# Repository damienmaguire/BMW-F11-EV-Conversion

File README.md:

# BMW-F11-EV-Conversion

Documenting the electronics and software side of converting a 2011 BMW 520d F11 (VIN: WBAMX12080V788571) to fully electric drive using a GS450h gearbox/inverter and ZombieVerter VCU.

## Project Goal – DDE FlexRay Emulator

The DDE (Diesel Engine Electronics) on this F11 talks to the rest of the car primarily over FlexRay. Once the diesel engine is removed, the cluster, gateway and other modules still expect to see a living DDE on the FlexRay network.

The plan is to build a small emulator that:

- Speaks FlexRay and CAN to the car
- Speaks CAN to the ZombieVerter VCU
- Translates the essential signals (RPM, coolant temp, fuel rate / power, status bits, etc.) so the car continues to behave normally
- Provides USB for programming and logging

Hardware target: one FlexRay channel + two CAN channels + USB.  
Bench development is being done with OpenFSD FlexRayRPIPanda boards and software based on dynm/pico-flexray, with SavvyCAN (flexray-phase1-capture branch) for capture and analysis.

## The DDE

- **BMW part number**: 8 513 250-01  
- **Bosch number**: 0 281 017 648  
- **Engine**: N47T 2.0 L diesel (520d)

FlexRay captures (ignition-on and engine start/stop) and later MITM logs are being used to reverse-engineer the frames the DDE sends and receives.

## FlexRay Capture Hardware / Software

- Hardware base: https://github.com/dynm/pico-flexray  
- SavvyCAN FlexRay branch: https://github.com/Tom-evnut/SavvyCAN/tree/flexray-phase1-capture  

Logs live in the `Logs/FlexRay` folder.

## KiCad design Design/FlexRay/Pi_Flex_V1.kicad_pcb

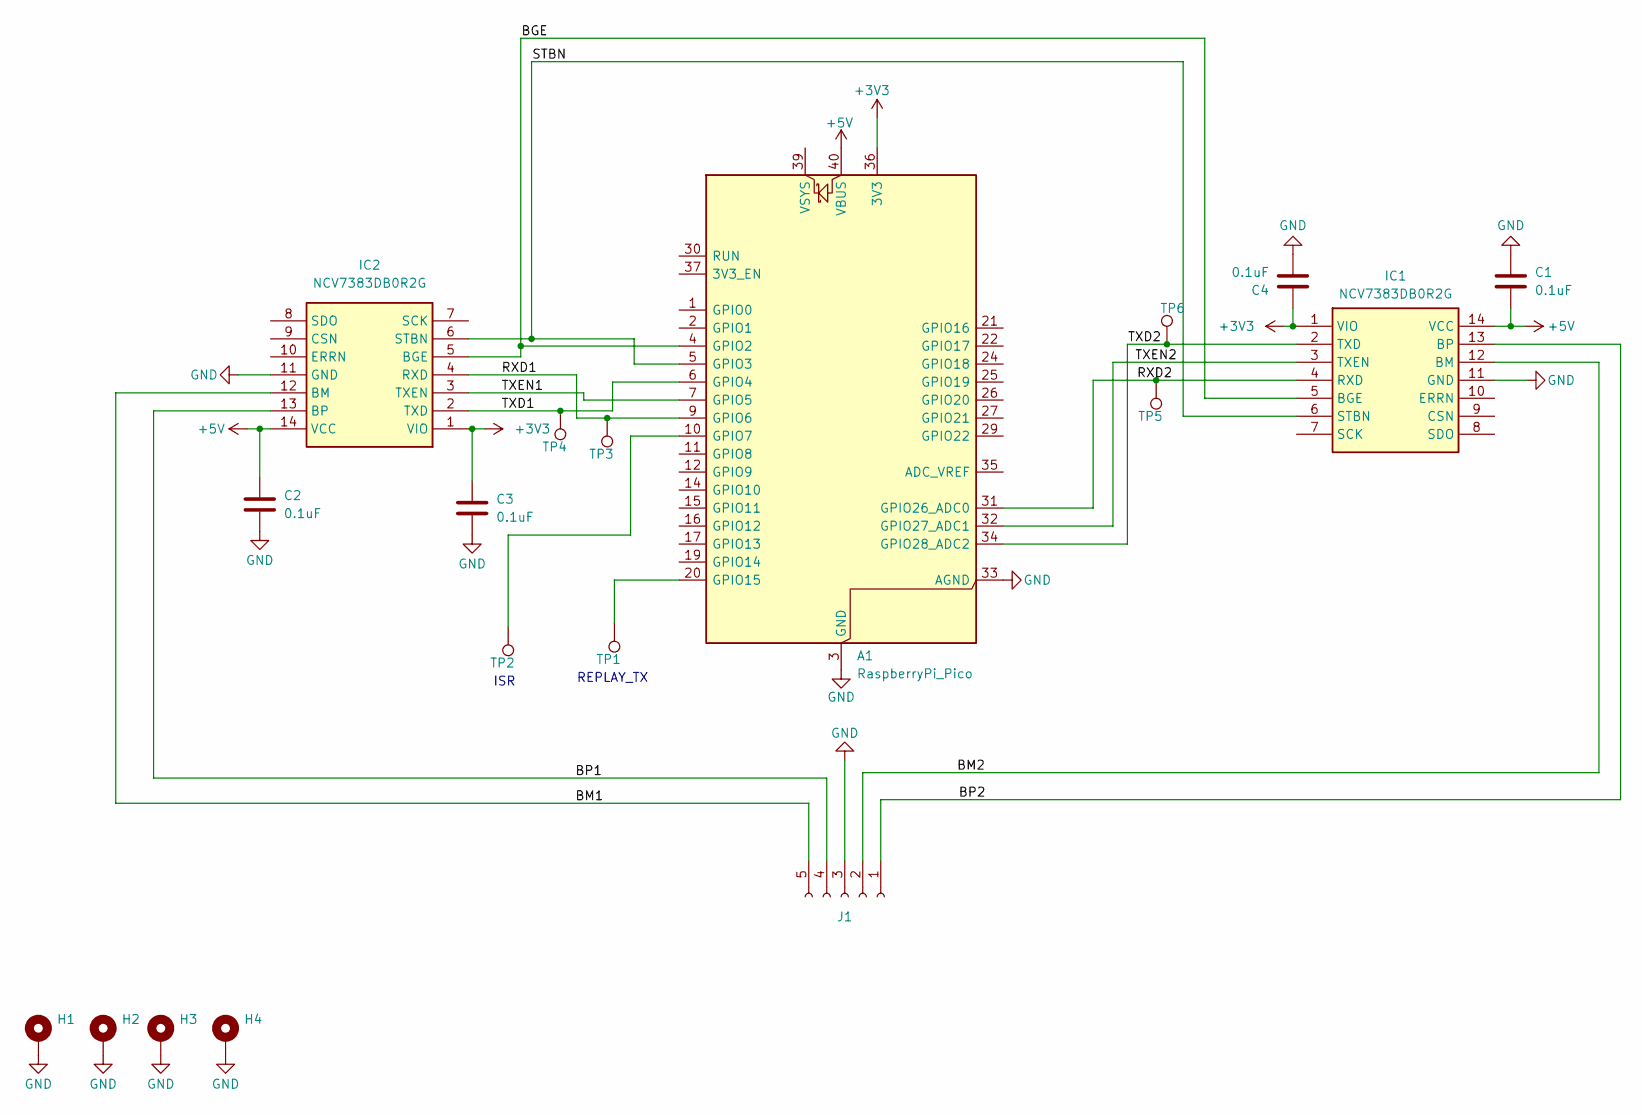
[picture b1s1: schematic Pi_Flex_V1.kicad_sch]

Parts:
A1: RaspberryPi_Pico; RaspberryPi_Pico_Common_Unspecified
C1, C2, C3, C4: 0.1uF; C_0805_2012Metric
H1, H2, H3, H4: MountingHole_Pad; MountingHole_6.4mm_M6_Pad_Via
IC1, IC2: NCV7383DB0R2G; TSSOP-14_4.4x5mm_P0.65mm; Manufacturer_Part_Number NCV7383DB0R2G; Mouser Part Number 863-NCV7383DB0R2G
J1: Conn_01x05_Socket; TerminalBlock_Xinya_XY308-2.54-5P_1x05_P2.54mm_Horizontal
TP1, TP2, TP3, TP4, TP5, TP6: TestPoint; TestPoint_THTPad_D2.5mm_Drill1.2mm

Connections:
+3V3: A1.36 (3V3), C3.1, C4.1, IC1.1 (VIO), IC2.1 (VIO)
+5V: A1.40 (VBUS), C1.2, C2.1, IC1.14 (VCC), IC2.14 (VCC)
/BGE: A1.4 (GPIO2), IC1.5 (BGE), IC2.5 (BGE)
/BM1: IC2.12 (BM), J1.5
/BM2: IC1.12 (BM), J1.2
/BP1: IC2.13 (BP), J1.4
/BP2: IC1.13 (BP), J1.1
/RXD1: A1.9 (GPIO6), IC2.4 (RXD), TP3.1
/RXD2: A1.31 (GPIO26_ADC0), IC1.4 (RXD), TP5.1
/STBN: A1.5 (GPIO3), IC1.6 (STBN), IC2.6 (STBN)
/TXD1: A1.6 (GPIO4), IC2.2 (TXD), TP4.1
/TXD2: A1.34 (GPIO28_ADC2), IC1.2 (TXD), TP6.1
/TXEN1: A1.7 (GPIO5), IC2.3 (TXEN)
/TXEN2: A1.32 (GPIO27_ADC1), IC1.3 (TXEN)
GND: A1.3 (GND), A1.8 (GND), A1.13 (GND), A1.18 (GND), A1.23 (GND), A1.28 (GND), A1.33 (AGND), A1.38 (GND), C1.1, C2.2, C3.2, C4.2, H1.1, H2.1, H3.1, H4.1, IC1.11 (GND), IC2.11 (GND), J1.3
unnamed: A1.10 (GPIO7), TP2.1
unnamed: A1.20 (GPIO15), TP1.1

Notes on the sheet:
ISR
REPLAY_TX

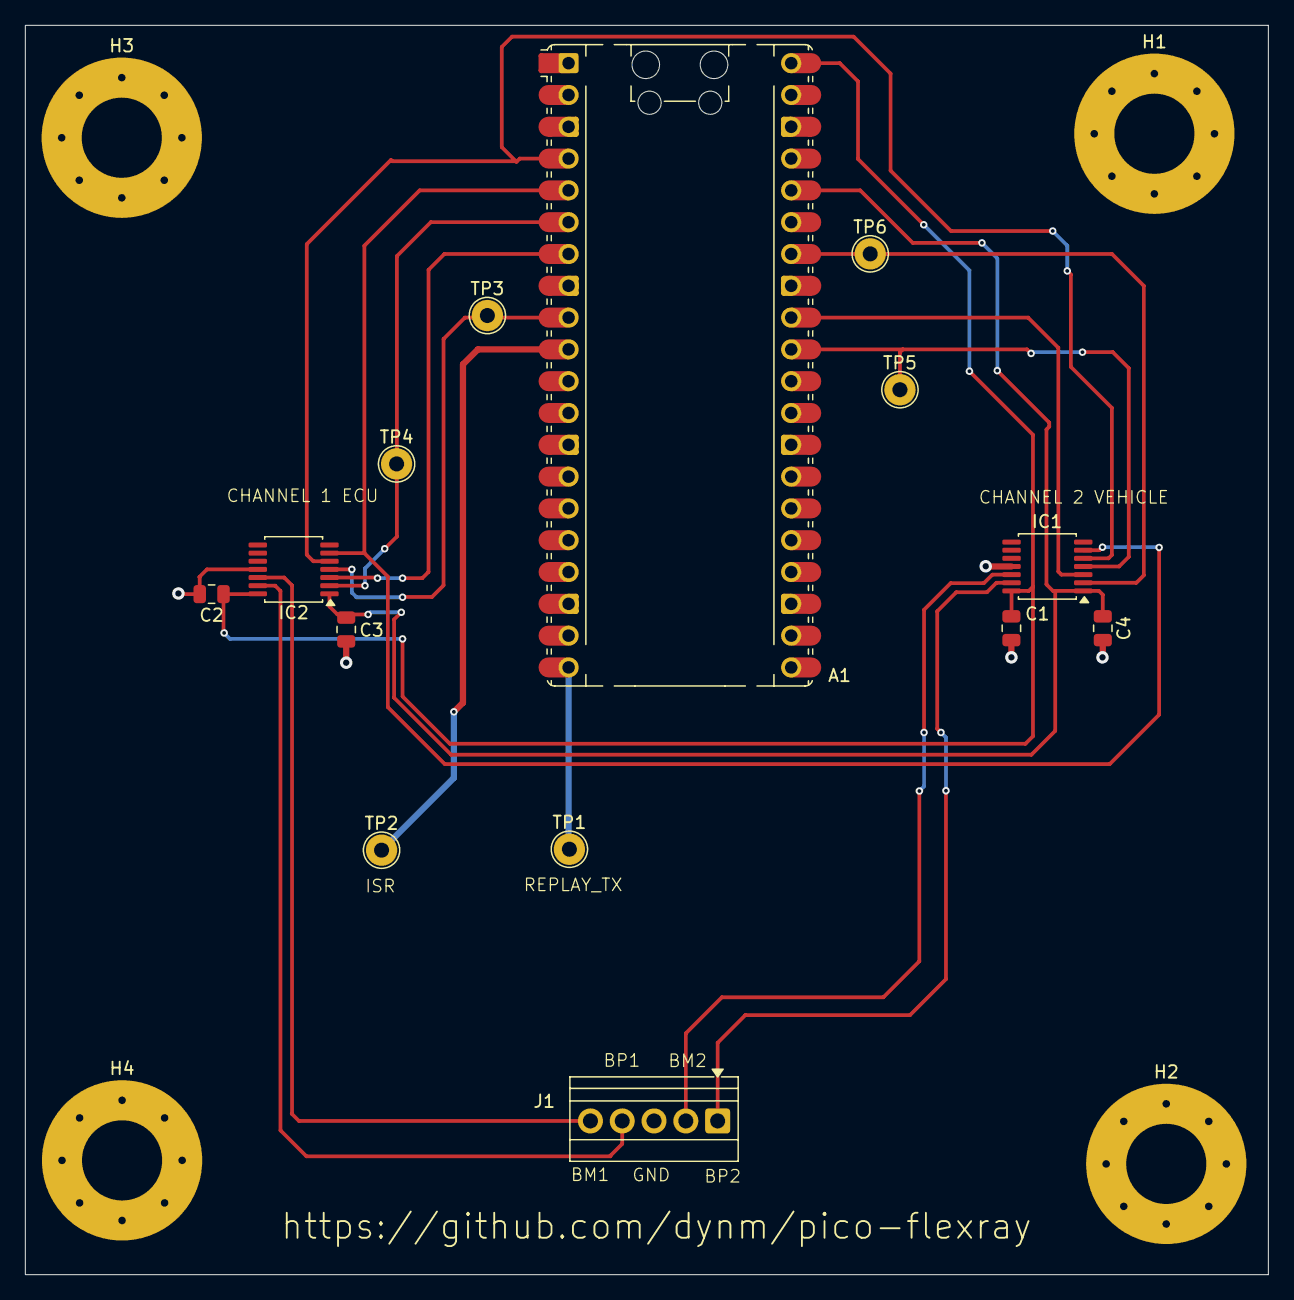
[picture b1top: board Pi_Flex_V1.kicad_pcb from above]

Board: 2 copper layers, 99.3 x 99.8 mm, 18 parts (0 on the bottom side), 17 nets.

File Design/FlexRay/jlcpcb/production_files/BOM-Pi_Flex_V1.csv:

Comment,Designator,Footprint,LCSC,Quantity
0.1uF,"C1,C2,C3,C4",C_0805_2012Metric,C126469,4
NCV7383DB0R2G,"IC1,IC2",TSSOP-14_4.4x5mm_P0.65mm,C904660,2
RaspberryPi_Pico,A1,RaspberryPi_Pico_Common_Unspecified,C41407547,1
